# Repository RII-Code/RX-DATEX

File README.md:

# RX-DATEX (DATA EXCHANGE)

Perangkat IoT industrial yang berfungsi sebagai sistem gateway dan data exchange untuk komunikasi, monitoring, dan pertukaran data antar perangkat industri.

## Fitur

- Gateway Modbus RTU ↔ TCP/IP
- Pengirim data telemetry melalui jaringan 4G LTE
- Sistem monitoring device industri
- Data logger dan remote monitoring
- MQTT / HTTP data exchange
- Remote access dan konfigurasi perangkat

---

## Author

Ruang Industri Indonesia  
Industrial Automation & Robotics

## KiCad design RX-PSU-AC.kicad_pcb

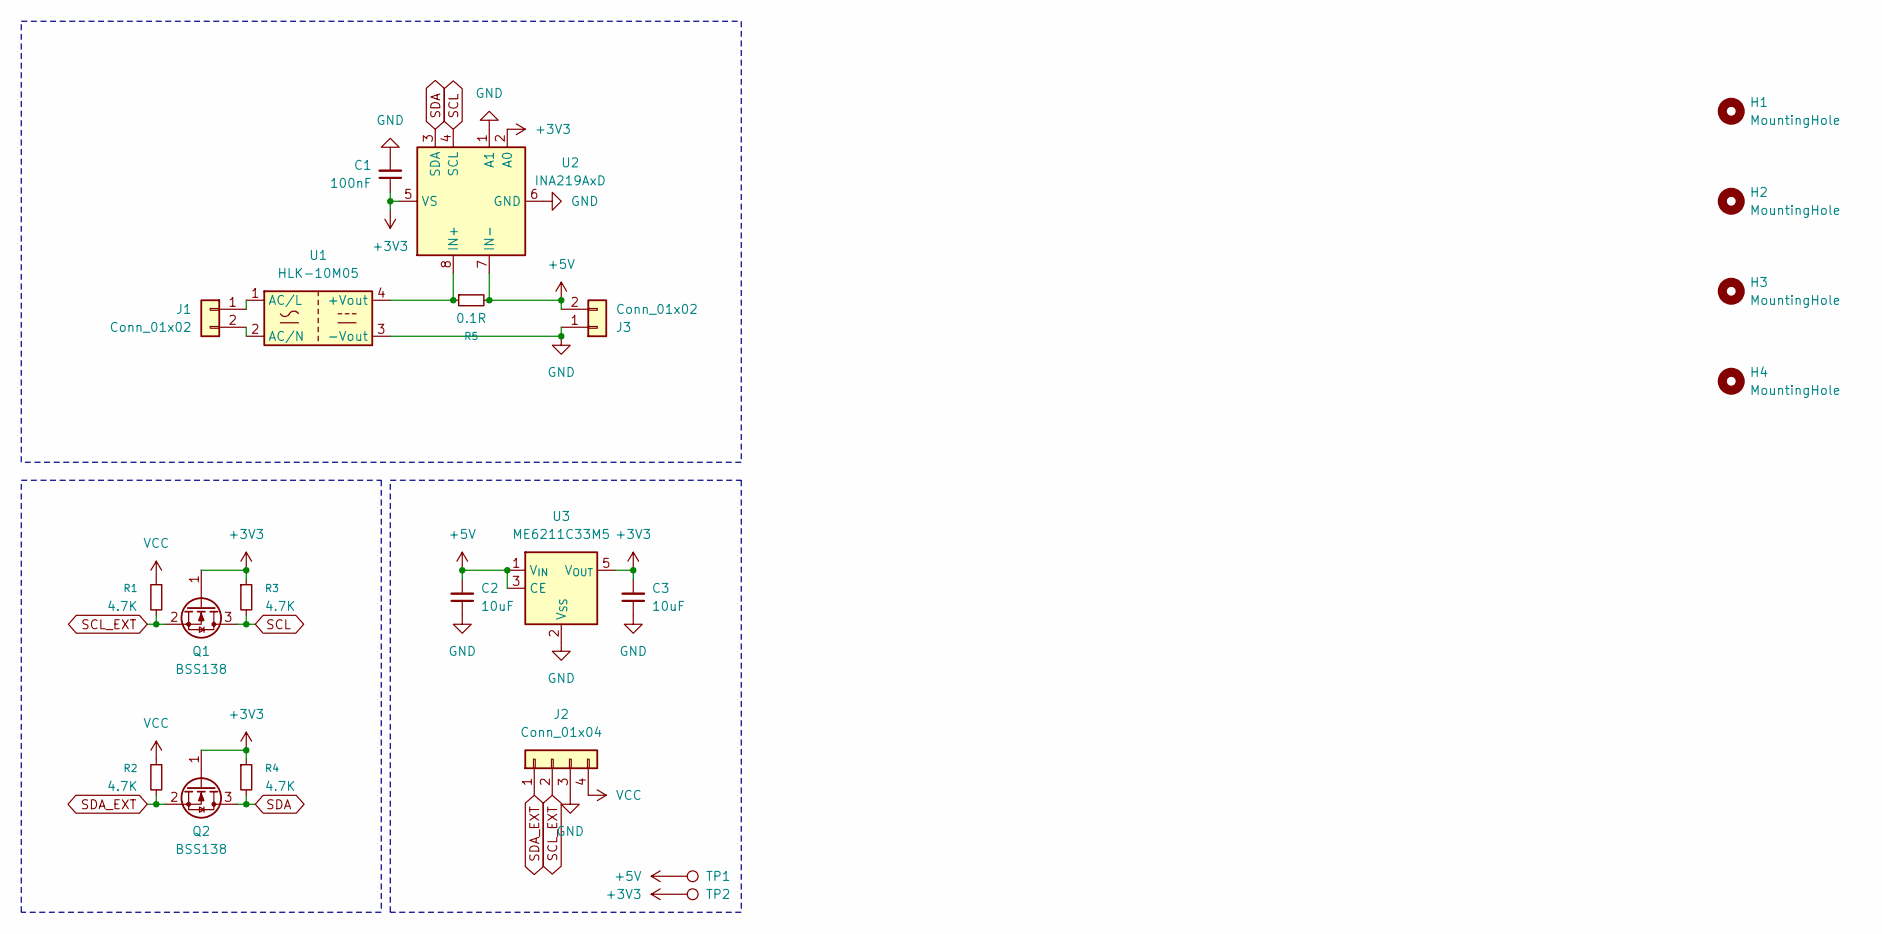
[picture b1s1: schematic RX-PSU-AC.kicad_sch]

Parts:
C1: 100nF; C_0805_2012Metric
C2, C3: 10uF; C_1206_3216Metric
H1, H2, H3, H4: MountingHole; MountingHole_3mm
J1: Conn_01x02; PhoenixContact_MC_1,5_2-G-5.08_1x02_P5.08mm_Horizontal
J2: Conn_01x04; JST_XH_B4B-XH-A_1x04_P2.50mm_Vertical
J3: Conn_01x02; JST_XH_B2B-XH-A_1x02_P2.50mm_Vertical
Q1, Q2: BSS138; SOT-23
R1, R2, R3, R4: 4.7K; R_0805_2012Metric
R5: 0.1R; R_2512_6332Metric
TP1, TP2: TestPoint; TestPoint_Pad_D1.0mm
U1: HLK-10M05; Converter_ACDC_Hi-Link_HLK-10Mxx
U2: INA219AxD; SOIC-8_3.9x4.9mm_P1.27mm
U3: ME6211C33M5; SOT-23-5

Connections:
+3V3: C1.1, C3.2, Q1.1 (G), Q2.1 (G), R3.1, R4.1, TP2.1 (1_1), U2.2 (A0), U2.5 (VS), U3.5 (V_{OUT})
+5V: C2.2, J3.2, R5.2, TP1.1 (1_1), U2.7 (IN-), U3.1 (V_{IN}), U3.3 (CE)
GND: C1.2, C2.1, C3.1, J2.3, J3.1, U1.3 (-Vout), U2.1 (A1), U2.6 (GND), U3.2 (V_{SS})
unnamed: J1.1, U1.1 (AC/L)
unnamed: J1.2, U1.2 (AC/N)
unnamed: R5.1, U1.4 (+Vout), U2.8 (IN+)
SCL: Q1.3 (D), R3.2, U2.4 (SCL)
SCL_EXT: J2.2, Q1.2 (S), R1.2
SDA: Q2.3 (D), R4.2, U2.3 (SDA)
SDA_EXT: J2.1, Q2.2 (S), R2.2
VCC: J2.4, R1.1, R2.1

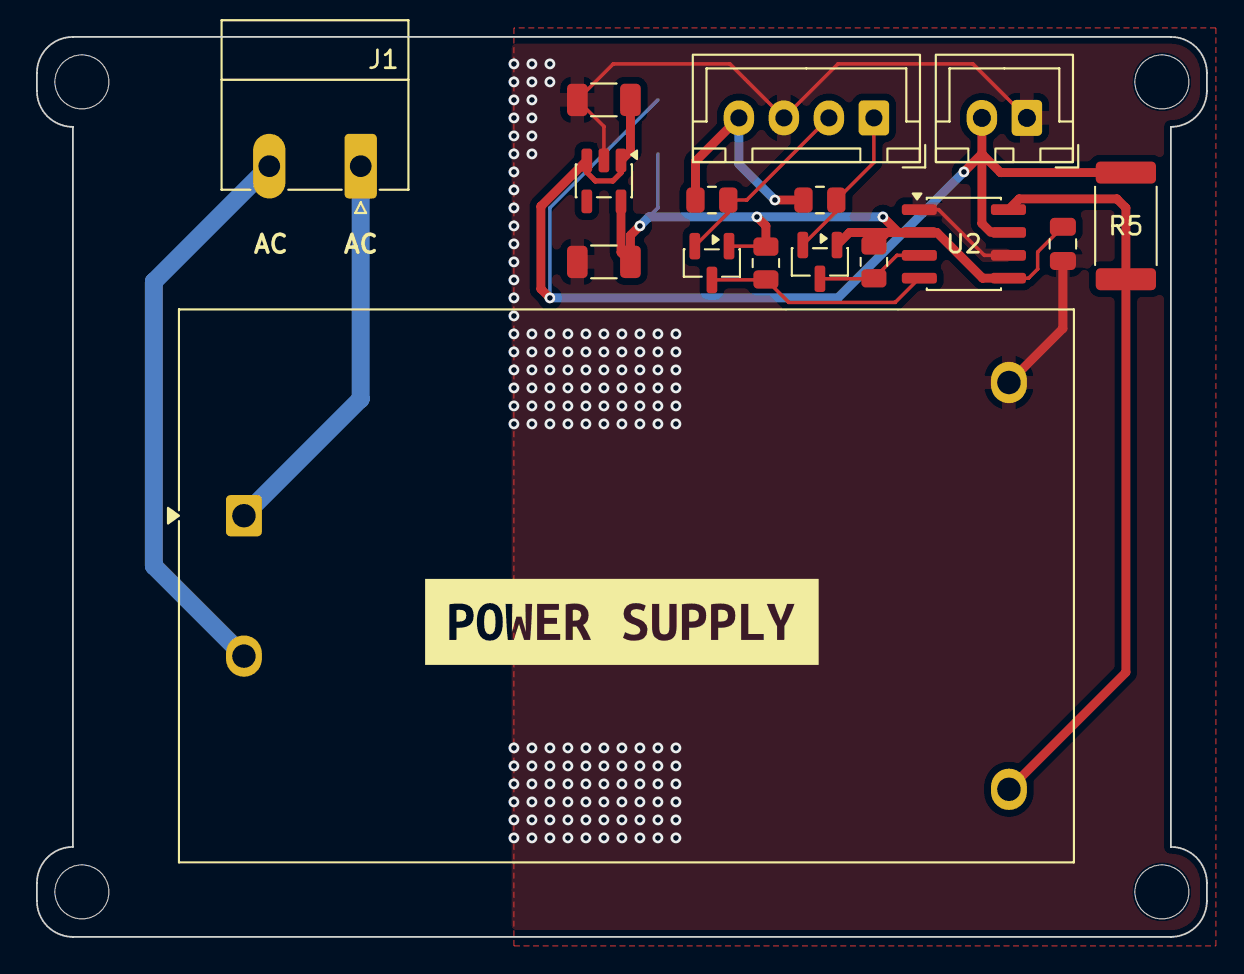
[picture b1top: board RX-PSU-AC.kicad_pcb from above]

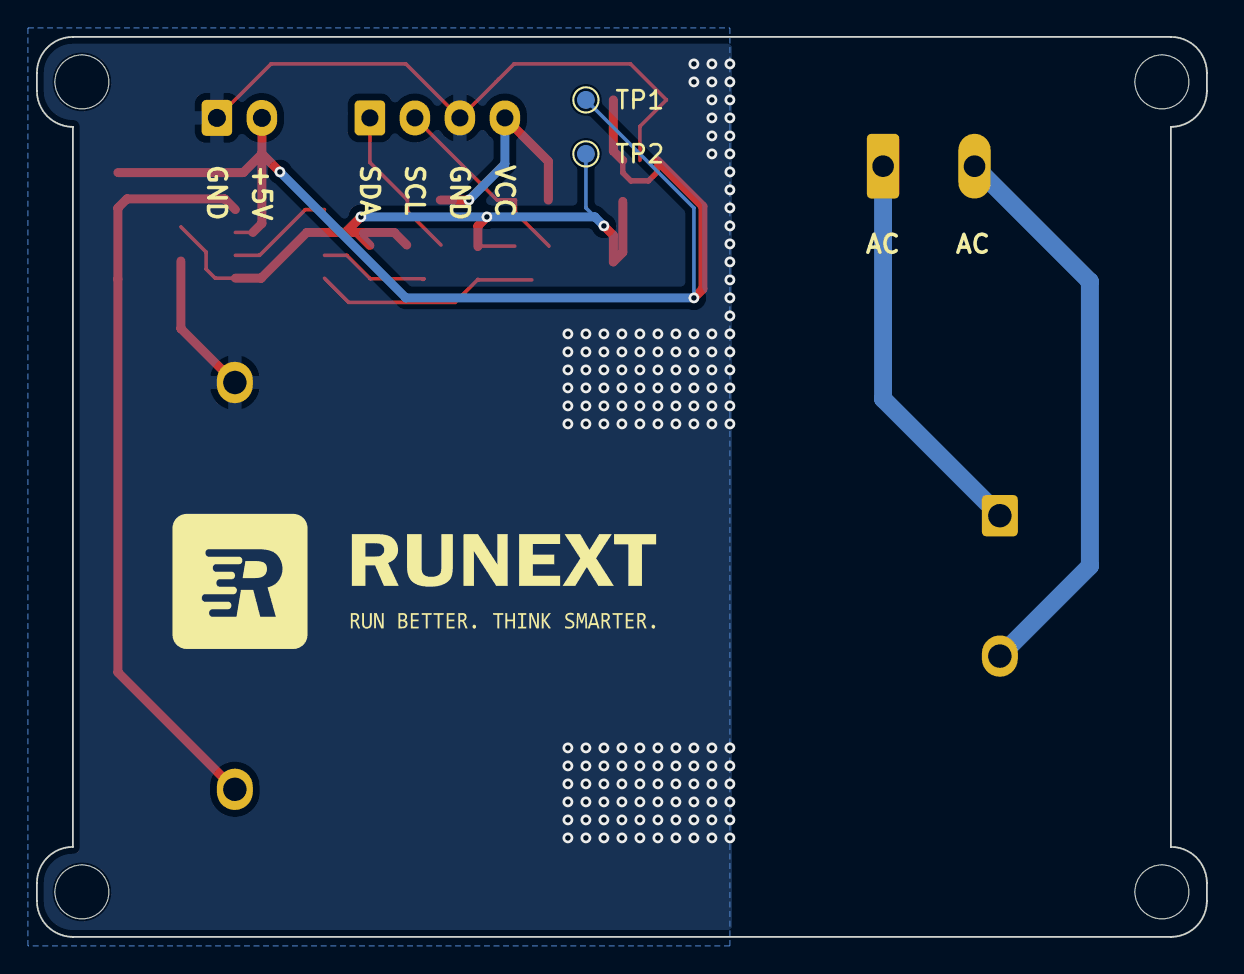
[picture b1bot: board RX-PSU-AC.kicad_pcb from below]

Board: 2 copper layers, 65.0 x 50.0 mm, 23 parts (2 on the bottom side), 11 nets.

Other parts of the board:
kibuzzard-6A0C9131: G***; kibuzzard-6A0C9131

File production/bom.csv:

Designator,Footprint,Quantity,Value,LCSC Part #
C1,0805,1,100nF,
"C2, C3",1206,2,10uF,
J1,"PhoenixContact_MC_1,5_2-G-5.08_1x02_P5.08mm_Horizontal",1,Conn_01x02,
J2,JST_XH_B4B-XH-A_1x04_P2.50mm_Vertical,1,Conn_01x04,
J3,JST_XH_B2B-XH-A_1x02_P2.50mm_Vertical,1,Conn_01x02,
"Q1, Q2",SOT-23,2,BSS138,
"R1, R2, R3, R4",0805,4,4.7K,
R5,2512,1,0.1R,
"TP1, TP2",TestPoint_Pad_D1.0mm,2,TestPoint,
U1,Converter_ACDC_Hi-Link_HLK-10Mxx,1,HLK-10M05,
U2,SOIC-8_3.9x4.9mm_P1.27mm,1,INA219AxD,
U3,SOT-23-5,1,ME6211C33M5,

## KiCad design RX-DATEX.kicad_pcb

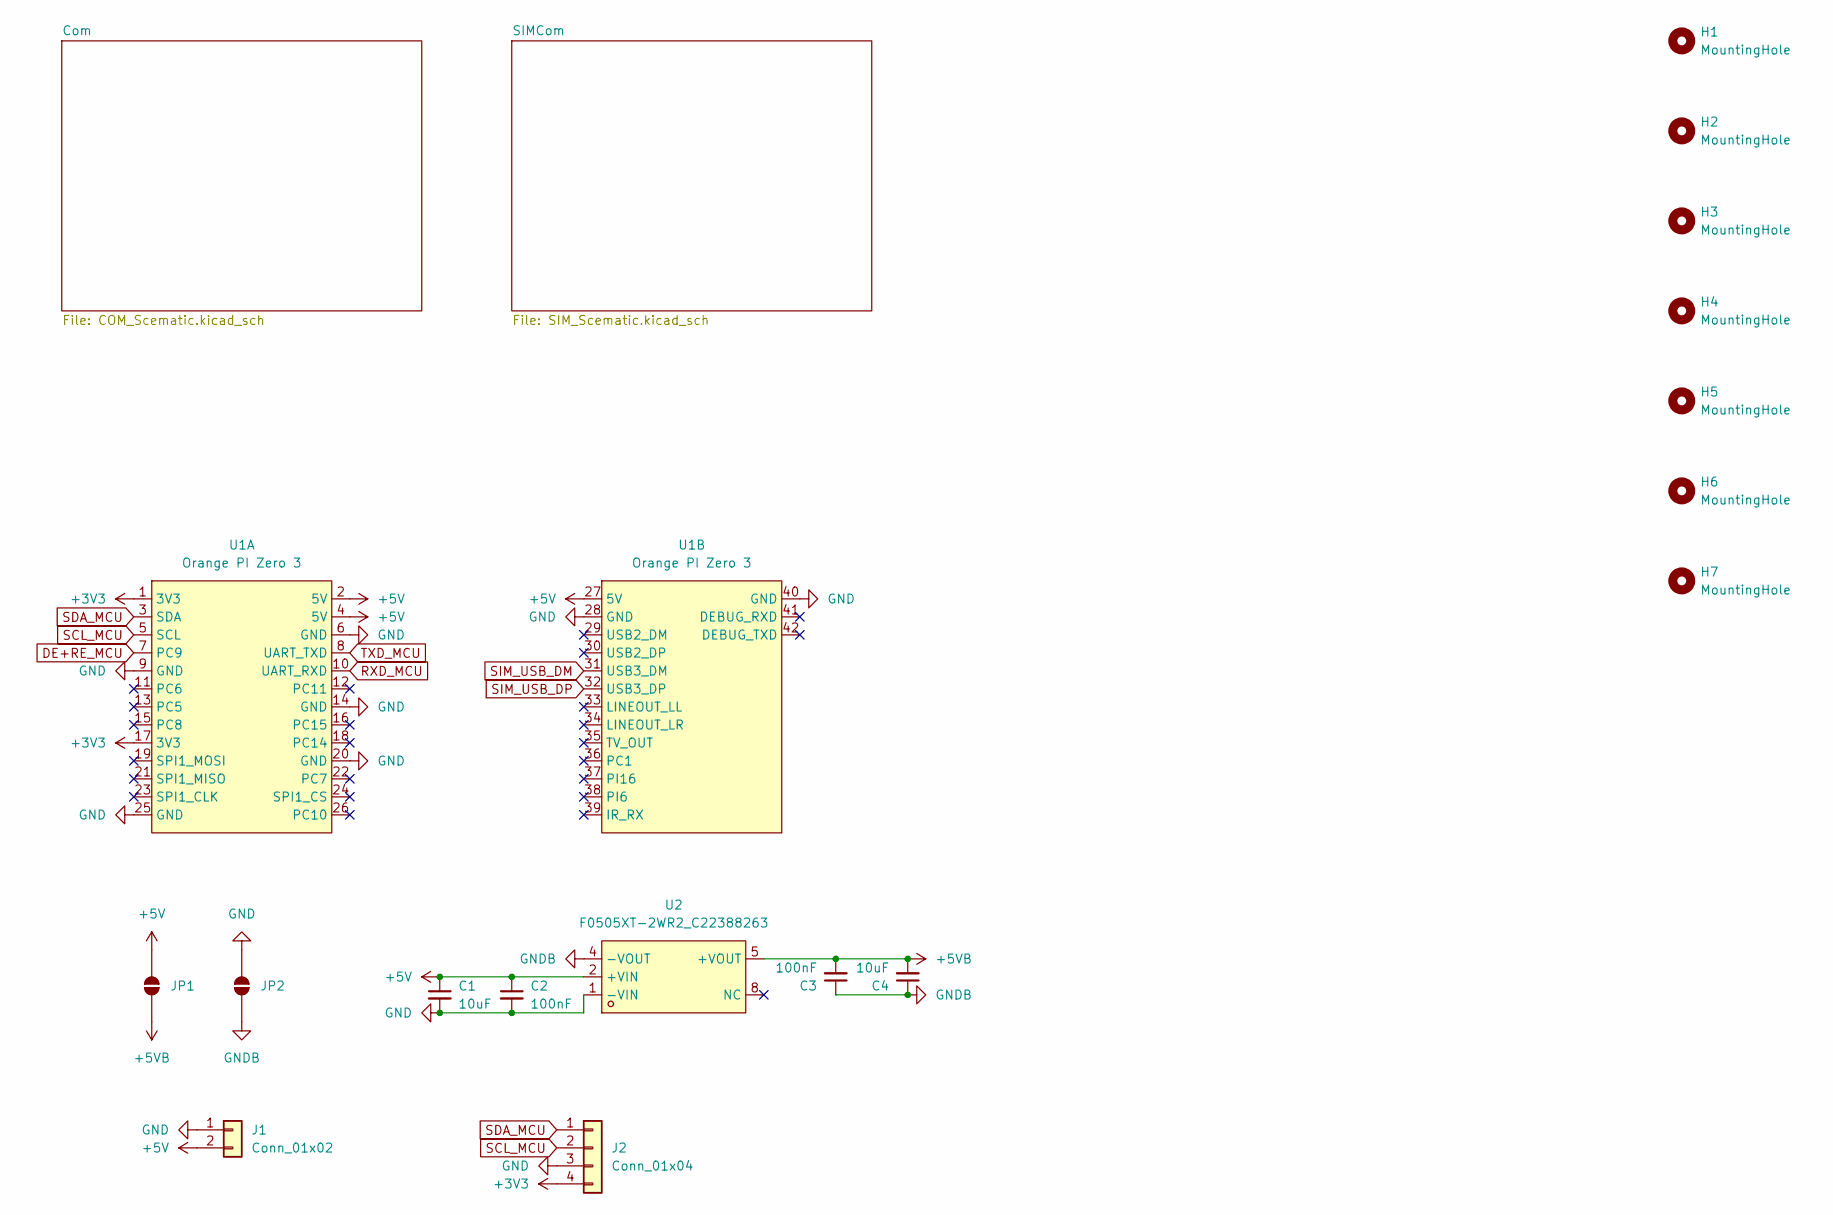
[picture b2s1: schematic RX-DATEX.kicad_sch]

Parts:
C1, C4: 10uF; C_0603_1608Metric
C2, C3: 100nF; C_0603_1608Metric
H1, H2, H3, H4, H5, H6, H7: MountingHole; MountingHole_3mm
J1: Conn_01x02; JST_XH_B2B-XH-A_1x02_P2.50mm_Vertical
J2: Conn_01x04; JST_XH_B4B-XH-A_1x04_P2.50mm_Vertical
JP1, JP2: SolderJumper_2_Open; SolderJumper-2_P1.3mm_Open_RoundedPad1.0x1.5mm
U1: Orange PI Zero 3; OPIZ3
U2: F0505XT-2WR2_C22388263; PWRM-SMD_FXXXXXT-2WR2; MPN F0505XT-2WR2; LCSC Part C22388263

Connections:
+3V3: J2.4, U1.1 (3V3), U1.17 (3V3); also elsewhere on the board
+5V: C1.1, C2.1, J1.2, JP1.2 (B), U1.2 (5V), U1.4 (5V), U1.27 (5V), U2.2 (+VIN); also elsewhere on the board
+5VB: C3.2, C4.2, JP1.1 (A), U2.5 (+VOUT); also elsewhere on the board
DE+RE_MCU: U1.7 (PC9); also elsewhere on the board
GND: C1.2, C2.2, J1.1, J2.3, JP2.2 (B), U1.6 (GND), U1.9 (GND), U1.14 (GND), U1.20 (GND), U1.25 (GND), U1.28 (GND), U1.40 (GND), U2.1 (-VIN); also elsewhere on the board
GNDB: C3.1, C4.1, JP2.1 (A), U2.4 (-VOUT); also elsewhere on the board
RXD_MCU: U1.10 (UART_RXD); also elsewhere on the board
SCL_MCU: J2.2, U1.5 (SCL); also elsewhere on the board
SDA_MCU: J2.1, U1.3 (SDA); also elsewhere on the board
SIM_USB_DM: U1.31 (USB3_DM); also elsewhere on the board
SIM_USB_DP: U1.32 (USB3_DP); also elsewhere on the board
TXD_MCU: U1.8 (UART_TXD); also elsewhere on the board

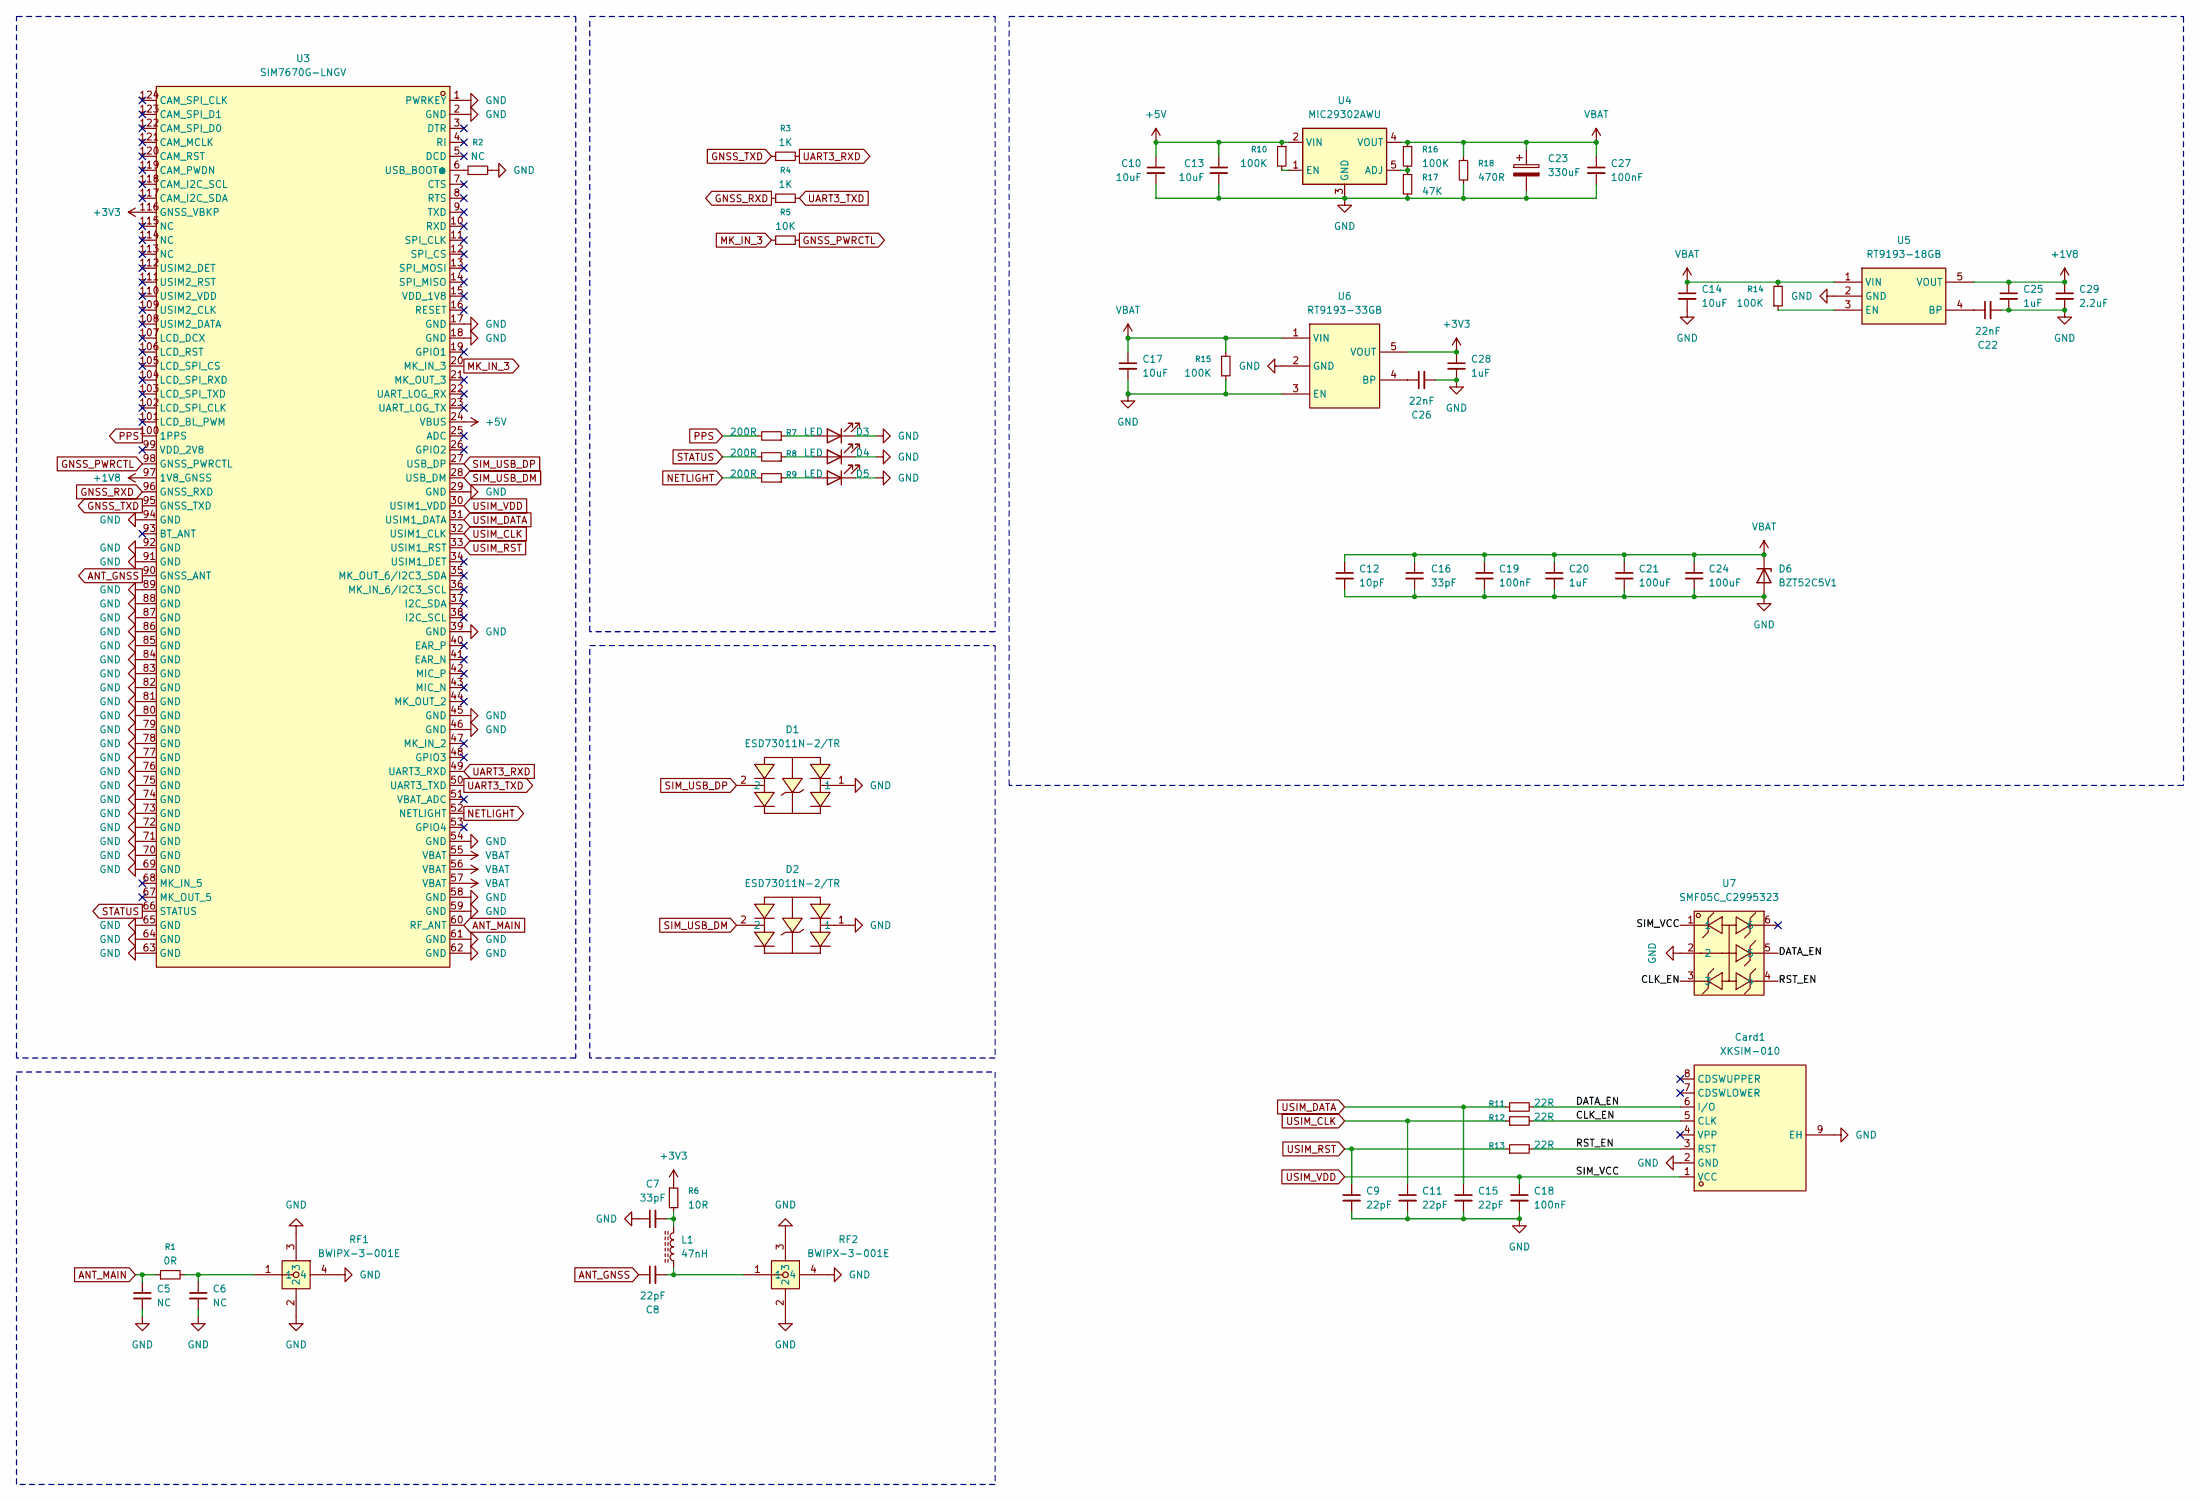
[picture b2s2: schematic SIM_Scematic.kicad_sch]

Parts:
C5, C6: NC; C_0603_1608Metric
C7, C16: 33pF; C_0603_1608Metric
C8, C9, C11, C15: 22pF; C_0603_1608Metric
C10, C13, C14, C17: 10uF; C_0603_1608Metric
C12: 10pF; C_0603_1608Metric
C18, C19, C27: 100nF; C_0603_1608Metric
C20, C25, C28: 1uF; C_0603_1608Metric
C21, C24: 100uF; C_0805_2012Metric
C22, C26: 22nF; C_0603_1608Metric
C23: 330uF; CP_EIA-7343-31_Kemet-D
C29: 2.2uF; C_0603_1608Metric
Card1: XKSIM-010; SIM-SMD_XKSIM-010; MPN XKSIM-010; LCSC Part C437039
D1, D2: ESD73011N-2/TR; DFN1006-2L-BI; MPN ESD73011N-2/TR; LCSC Part C506104
D3, D4, D5: LED; LED_1206_3216Metric
D6: BZT52C5V1; D_SOD-123
L1: 47nH; L_0603_1608Metric
R1: 0R; R_0603_1608Metric
R2: NC; R_0603_1608Metric
R3, R4: 1K; R_0603_1608Metric
R5: 10K; R_0603_1608Metric
R6: 10R; R_0603_1608Metric
R7, R8, R9: 200R; R_0603_1608Metric
R10, R14, R15, R16: 100K; R_0603_1608Metric
R11, R12, R13: 22R; R_0603_1608Metric
R17: 47K; R_0603_1608Metric
R18: 470R; R_0603_1608Metric
RF1, RF2: BWIPX-3-001E; IPEX-SMD_BWIPX-3-001E-1; MPN BWIPX-3-001E; LCSC Part C784400
U3: SIM7670G-LNGV; LCC-124_L24.0-W24.0-P1.0-TL; MPN SIM7670G-LNGV; LCSC Part C45935408
U4: MIC29302AWU; TO-263-5_TabPin3
U5: RT9193-18GB; SOT-23-5_L3.0-W1.7-P0.95-LS2.8-BR; MPN RT9193-18GB; LCSC Part C27416
U6: RT9193-33GB; SOT-23-5_L3.0-W1.7-P0.95-LS2.8-BL; MPN RT9193-33GB; LCSC Part C15651
U7: SMF05C_C2995323; SOT-363_L2.1-W1.3-P0.65-LS2.1-BL; MPN SMF05C; LCSC Part C2995323

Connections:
+1V8: C25.1, C29.1, U3.97 (1V8_GNSS), U5.5 (VOUT)
+3V3: C28.1, R6.1, U3.116 (GNSS_VBKP), U6.5 (VOUT); also elsewhere on the board
+5V: C10.1, C13.1, R10.1, U3.24 (VBUS), U4.2 (VIN); also elsewhere on the board
/SIMCom/CLK_EN: Card1.5 (CLK), R12.2, U7.3
/SIMCom/DATA_EN: Card1.6 (I/O), R11.2, U7.5
/SIMCom/RST_EN: Card1.3 (RST), R13.2, U7.4
ANT_GNSS: C8.1, U3.90 (GNSS_ANT)
ANT_MAIN: C5.1, R1.1, U3.60 (RF_ANT)
GND: C5.2, C6.2, C7.1, C9.2, C10.2, C11.2, C12.2, C13.2, C14.2, C15.2, C16.2, C17.2, C18.2, C19.2, C20.2, C21.2, C22.2, C23.2, C24.2, C25.2, C26.2, C27.2, C28.2, C29.2, Card1.2 (GND), Card1.9 (EH), D1.1, D2.1, D3.1 (K), D4.1 (K), D5.1 (K), D6.2 (A), R2.2, R15.1, R17.2, R18.2, RF1.2, RF1.3, RF1.4, RF2.2, RF2.3, RF2.4, U3.1 (PWRKEY), U3.2 (GND), U3.17 (GND), U3.18 (GND), U3.29 (GND), U3.39 (GND), U3.45 (GND), U3.46 (GND), U3.54 (GND), U3.58 (GND), U3.59 (GND), U3.61 (GND), U3.62 (GND), U3.63 (GND), U3.64 (GND), U3.65 (GND), U3.69 (GND), U3.70 (GND), U3.71 (GND), U3.72 (GND), U3.73 (GND), U3.74 (GND), U3.75 (GND), U3.76 (GND), U3.77 (GND), U3.78 (GND), U3.79 (GND), U3.80 (GND), U3.81 (GND), U3.82 (GND), U3.83 (GND), U3.84 (GND), U3.85 (GND), U3.86 (GND), U3.87 (GND), U3.88 (GND), U3.89 (GND), U3.91 (GND), U3.92 (GND), U3.94 (GND), U4.3 (GND), U5.2 (GND), U6.2 (GND), U6.3 (EN), U7.2; also elsewhere on the board
GNSS_PWRCTL: R5.2, U3.98 (GNSS_PWRCTL)
GNSS_RXD: R4.1, U3.96 (GNSS_RXD)
GNSS_TXD: R3.1, U3.95 (GNSS_TXD)
MK_IN_3: R5.1, U3.20 (MK_IN_3)
NETLIGHT: R9.2, U3.52 (NETLIGHT)
unnamed: C6.1, R1.2, RF1.1
unnamed: C7.2, L1.2, R6.2
unnamed: C8.2, L1.1, RF2.1
unnamed: D3.2 (A), R7.1
unnamed: D4.2 (A), R8.1
unnamed: D5.2 (A), R9.1
unnamed: R2.1, U3.6 (USB_BOOT●)
unnamed: R16.2, R17.1, U4.5 (ADJ)
unnamed: R10.2, U4.1 (EN)
unnamed: C22.1, U5.4 (BP)
unnamed: R14.1, U5.3 (EN)
unnamed: C26.1, U6.4 (BP)
PPS: R7.2, U3.100 (1PPS)
SIM_USB_DM: D2.2, U3.28 (USB_DM); also elsewhere on the board
SIM_USB_DP: D1.2, U3.27 (USB_DP); also elsewhere on the board
STATUS: R8.2, U3.66 (STATUS)
UART3_RXD: R3.2, U3.49 (UART3_RXD)
UART3_TXD: R4.2, U3.50 (UART3_TXD)
USIM_CLK: C11.1, R12.1, U3.32 (USIM1_CLK)
USIM_DATA: C15.1, R11.1, U3.31 (USIM1_DATA)
USIM_RST: C9.1, R13.1, U3.33 (USIM1_RST)
USIM_VDD: C18.1, Card1.1 (VCC), U3.30 (USIM1_VDD), U7.1
VBAT: C12.1, C14.1, C16.1, C17.1, C19.1, C20.1, C21.1, C23.1, C24.1, C27.1, D6.1 (K), R14.2, R15.2, R16.1, R18.1, U3.55 (VBAT), U3.56 (VBAT), U3.57 (VBAT), U4.4 (VOUT), U5.1 (VIN), U6.1 (VIN)

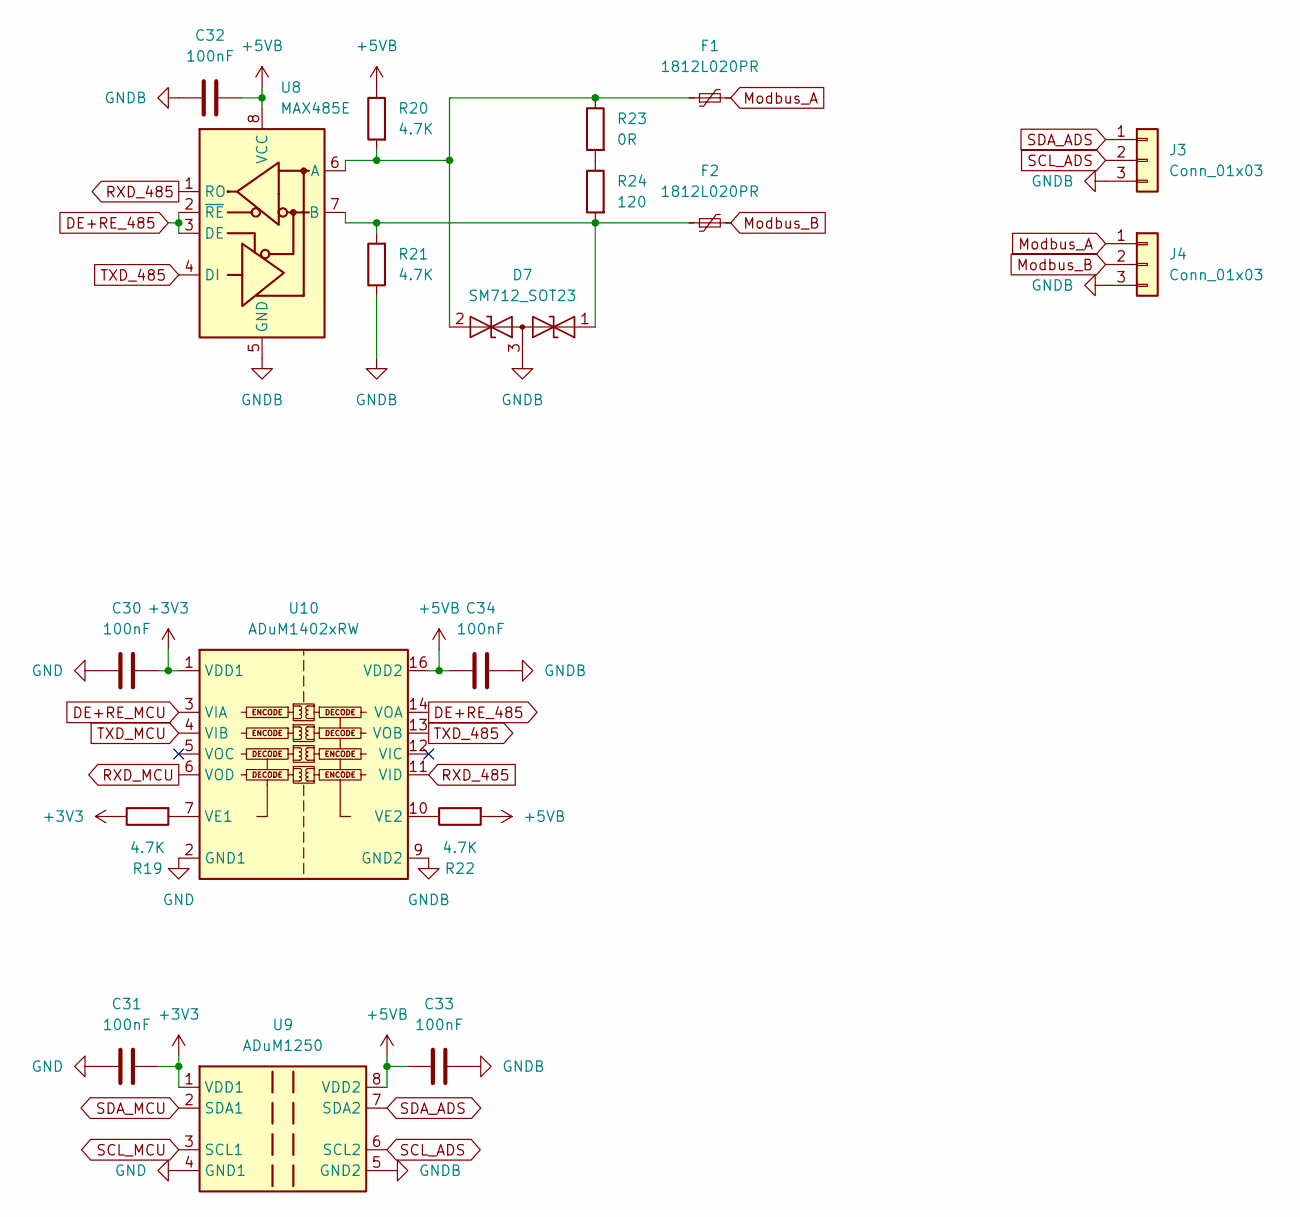
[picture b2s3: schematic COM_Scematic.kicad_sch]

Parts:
C30, C31, C32, C33, C34: 100nF; C_0603_1608Metric_Pad1.08x0.95mm_HandSolder
D7: SM712_SOT23; SOT-23
F1, F2: 1812L020PR; Fuse_1812_4532Metric
J3, J4: Conn_01x03; PhoenixContact_MC_1,5_3-G-3.81_1x03_P3.81mm_Horizontal
R19, R20, R21, R22: 4.7K; R_0603_1608Metric_Pad0.98x0.95mm_HandSolder
R23: 0R; R_0603_1608Metric_Pad0.98x0.95mm_HandSolder
R24: 120; R_0603_1608Metric_Pad0.98x0.95mm_HandSolder
U8: MAX485E; SOIC-8_3.9x4.9mm_P1.27mm
U9: ADuM1250; SOIC-8_3.9x4.9mm_P1.27mm
U10: ADuM1402xRW; SOIC-16W_7.5x10.3mm_P1.27mm

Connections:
+3V3: C30.2, C31.2, R19.1, U9.1 (VDD1), U10.1 (VDD1); also elsewhere on the board
+5VB: C32.2, C33.2, C34.2, R20.1, R22.2, U8.8 (VCC), U9.8 (VDD2), U10.16 (VDD2); also elsewhere on the board
DE+RE_485: U8.2 (~RE), U8.3 (DE), U10.14 (VOA)
DE+RE_MCU: U10.3 (VIA); also elsewhere on the board
GND: C30.1, C31.1, U9.4 (GND1), U10.2 (GND1), U10.8 (GND1); also elsewhere on the board
GNDB: C32.1, C33.1, C34.1, D7.3 (common), J3.3, J4.3, R21.1, U8.5 (GND), U9.5 (GND2), U10.9 (GND2), U10.15 (GND2); also elsewhere on the board
Modbus_A: F1.2, J4.1
Modbus_B: F2.2, J4.2
unnamed: D7.1 (A1), F2.1, R21.2, R24.2, U8.7 (B)
unnamed: D7.2 (A2), F1.1, R20.2, R23.1, U8.6 (A)
unnamed: R23.2, R24.1
unnamed: R19.2, U10.7 (VE1)
unnamed: R22.1, U10.10 (VE2)
RXD_485: U8.1 (RO), U10.11 (VID)
RXD_MCU: U10.6 (VOD); also elsewhere on the board
SCL_ADS: J3.2, U9.6 (SCL2)
SCL_MCU: U9.3 (SCL1); also elsewhere on the board
SDA_ADS: J3.1, U9.7 (SDA2)
SDA_MCU: U9.2 (SDA1); also elsewhere on the board
TXD_485: U8.4 (DI), U10.13 (VOB)
TXD_MCU: U10.4 (VIB); also elsewhere on the board

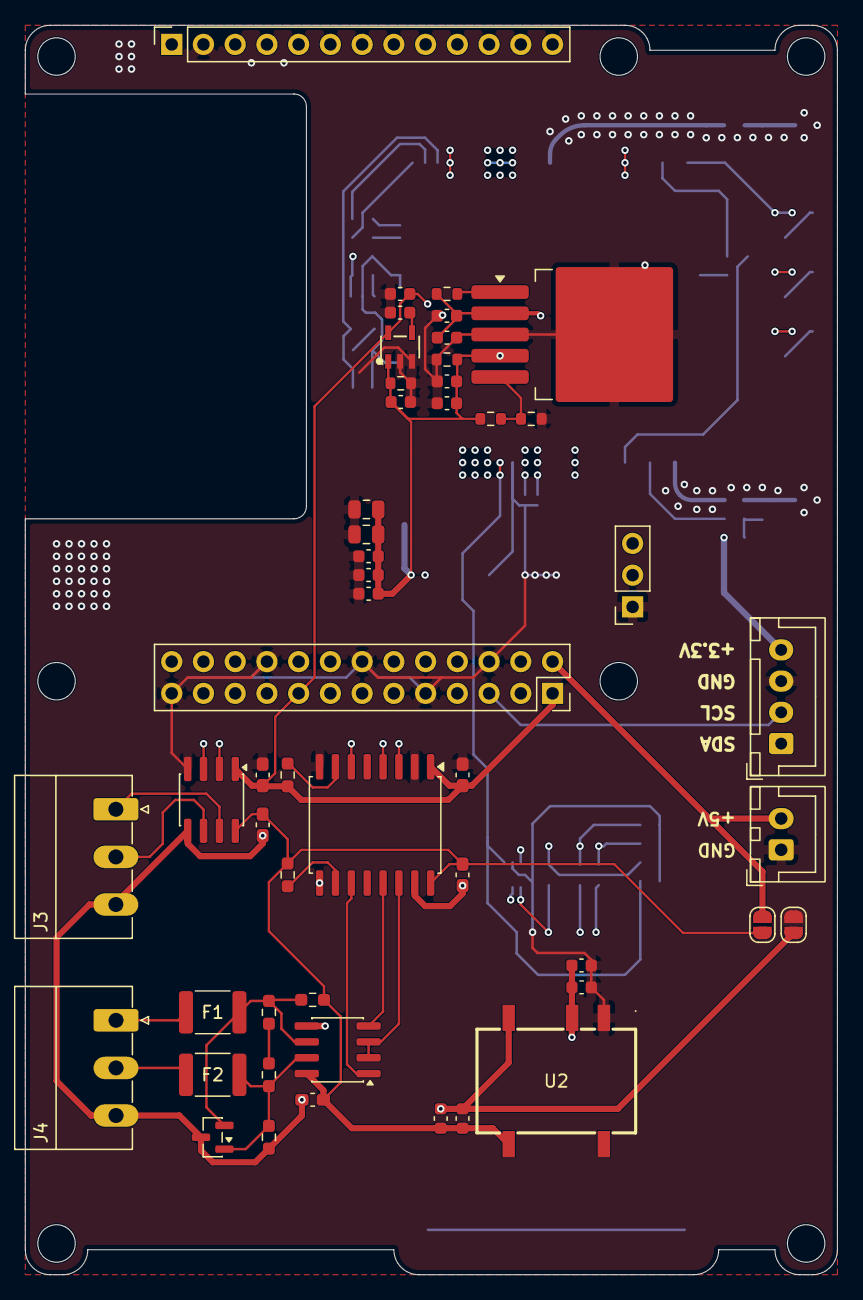
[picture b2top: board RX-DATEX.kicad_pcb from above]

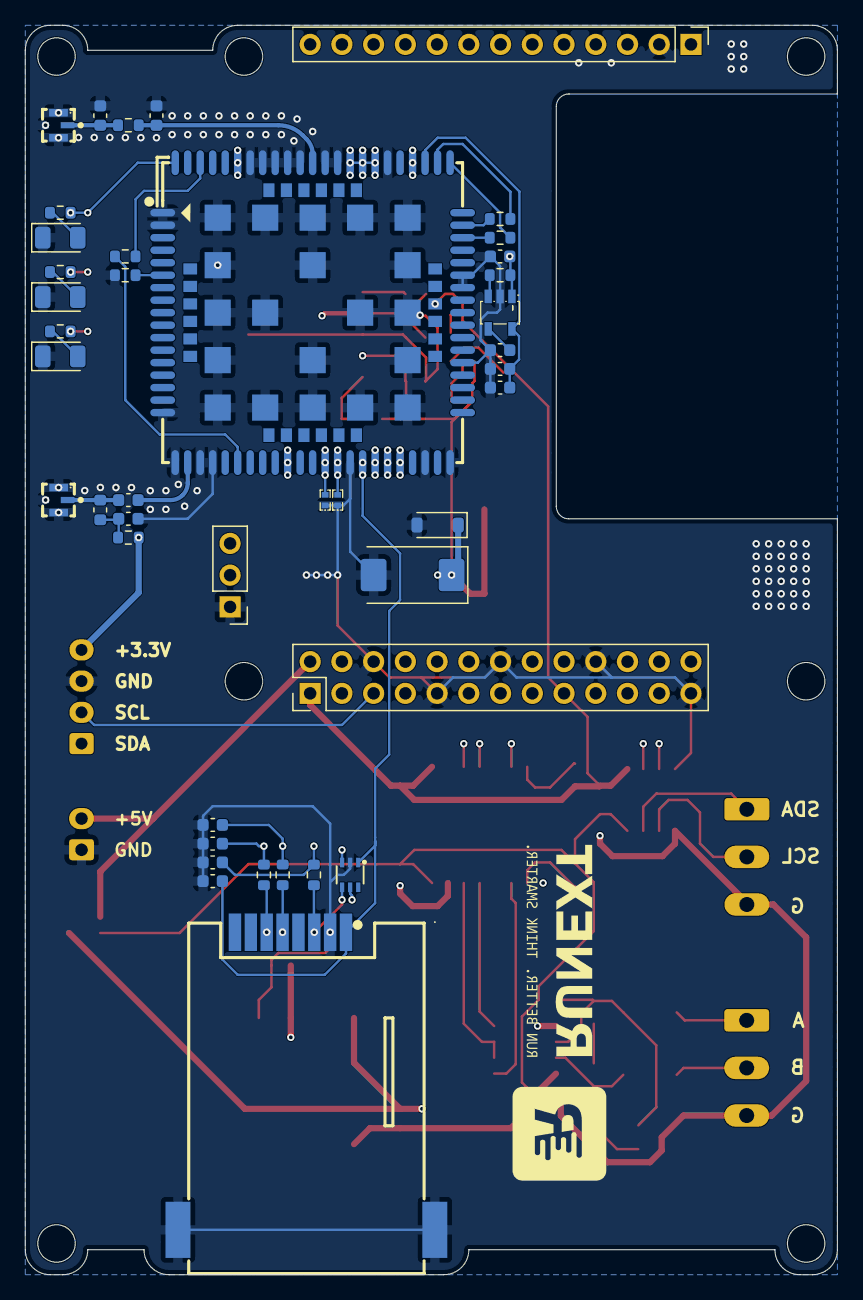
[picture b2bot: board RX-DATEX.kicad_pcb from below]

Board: 4 copper layers, 65.0 x 100.0 mm, 94 parts (40 on the bottom side), 56 nets.

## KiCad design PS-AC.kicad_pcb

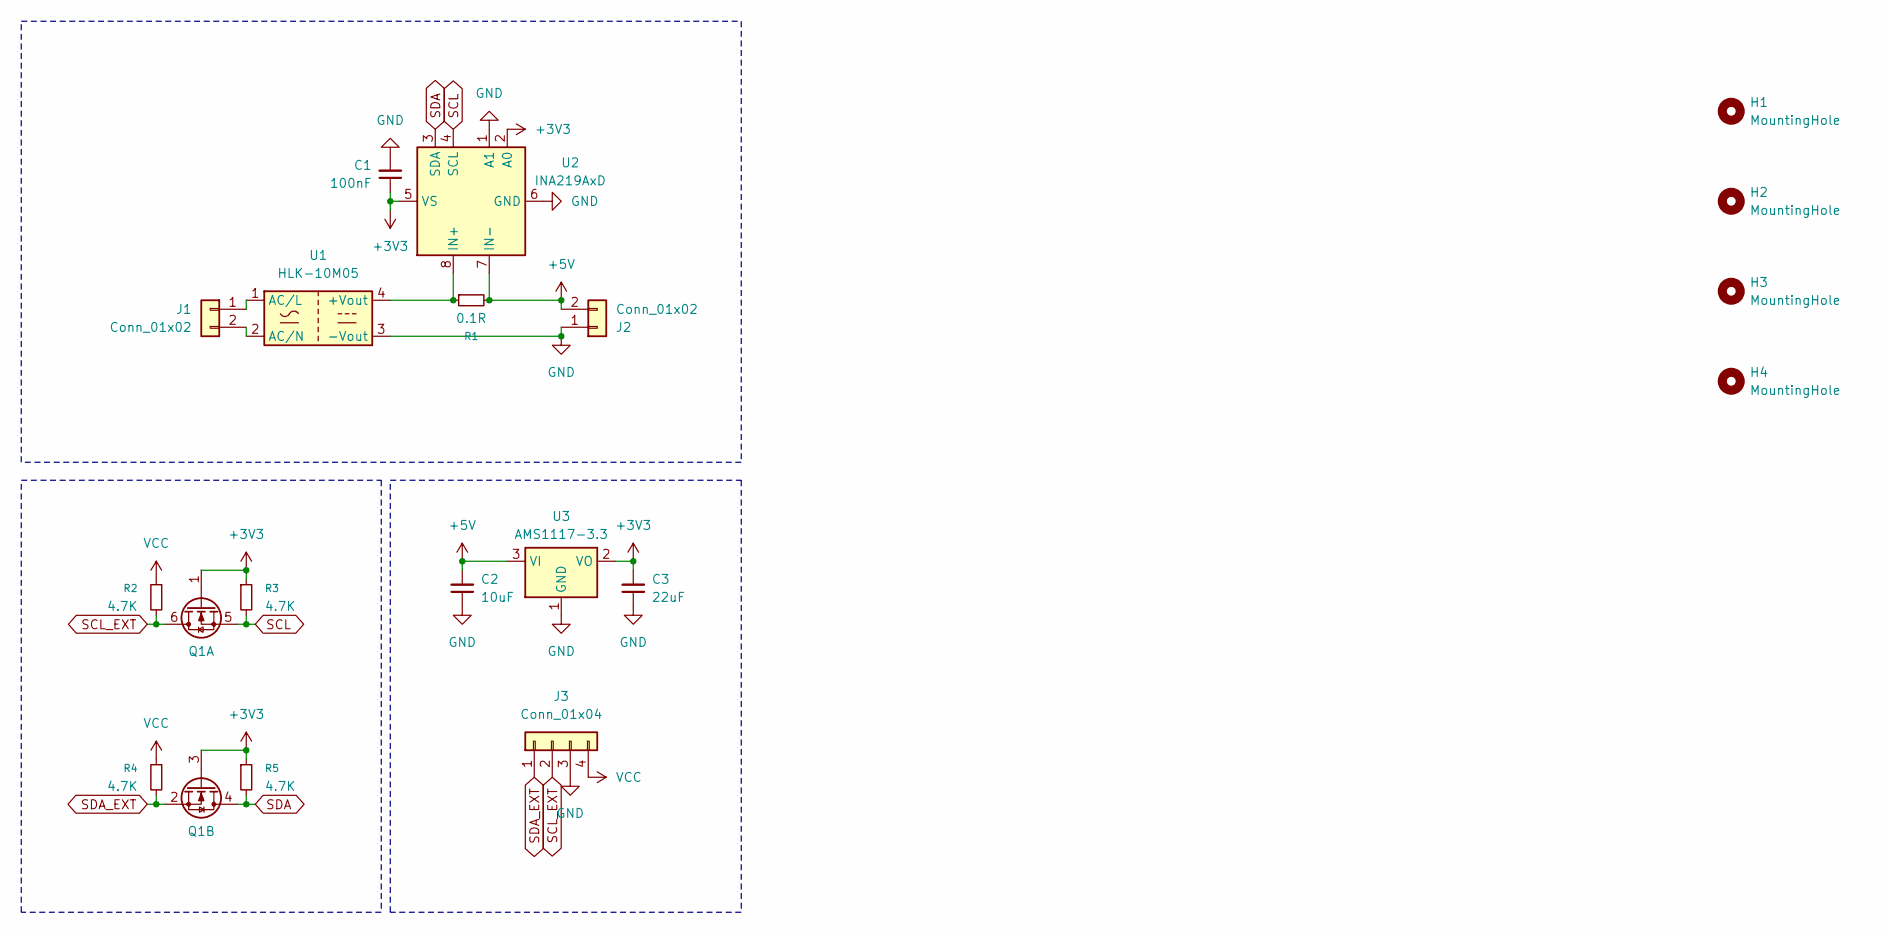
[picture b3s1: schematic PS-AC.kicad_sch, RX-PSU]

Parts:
C1: 100nF; C_0603_1608Metric
C2: 10uF; C_0603_1608Metric
C3: 22uF; C_0603_1608Metric
H1, H2, H3, H4: MountingHole; MountingHole_3mm
J1: Conn_01x02; PhoenixContact_MC_1,5_2-G-5.08_1x02_P5.08mm_Horizontal
J2: Conn_01x02; JST_XH_B2B-XH-A_1x02_P2.50mm_Vertical
J3: Conn_01x04; JST_XH_B4B-XH-A_1x04_P2.50mm_Vertical
Q1: NTZD3154NT1G; SOT-563
R1: 0.1R; R_1206_3216Metric
R2, R3, R4, R5: 4.7K; R_0603_1608Metric
U1: HLK-10M05; Converter_ACDC_Hi-Link_HLK-10Mxx
U2: INA219AxD; SOIC-8_3.9x4.9mm_P1.27mm
U3: AMS1117-3.3; SOT-223-3_TabPin2

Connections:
+3V3: C1.1, C3.2, Q1.1 (G), Q1.3 (G), R3.1, R5.1, U2.2 (A0), U2.5 (VS), U3.2 (VO)
+5V: C2.2, J2.2, R1.2, U2.7 (IN-), U3.3 (VI)
GND: C1.2, C2.1, C3.1, J2.1, J3.3, U1.3 (-Vout), U2.1 (A1), U2.6 (GND), U3.1 (GND)
unnamed: J1.1, U1.1 (AC/L)
unnamed: J1.2, U1.2 (AC/N)
unnamed: R1.1, U1.4 (+Vout), U2.8 (IN+)
SCL: Q1.5 (S), R3.2, U2.4 (SCL)
SCL_EXT: J3.2, Q1.6 (D), R2.2
SDA: Q1.4 (D), R5.2, U2.3 (SDA)
SDA_EXT: J3.1, Q1.2 (S), R4.2
VCC: J3.4, R2.1, R4.1

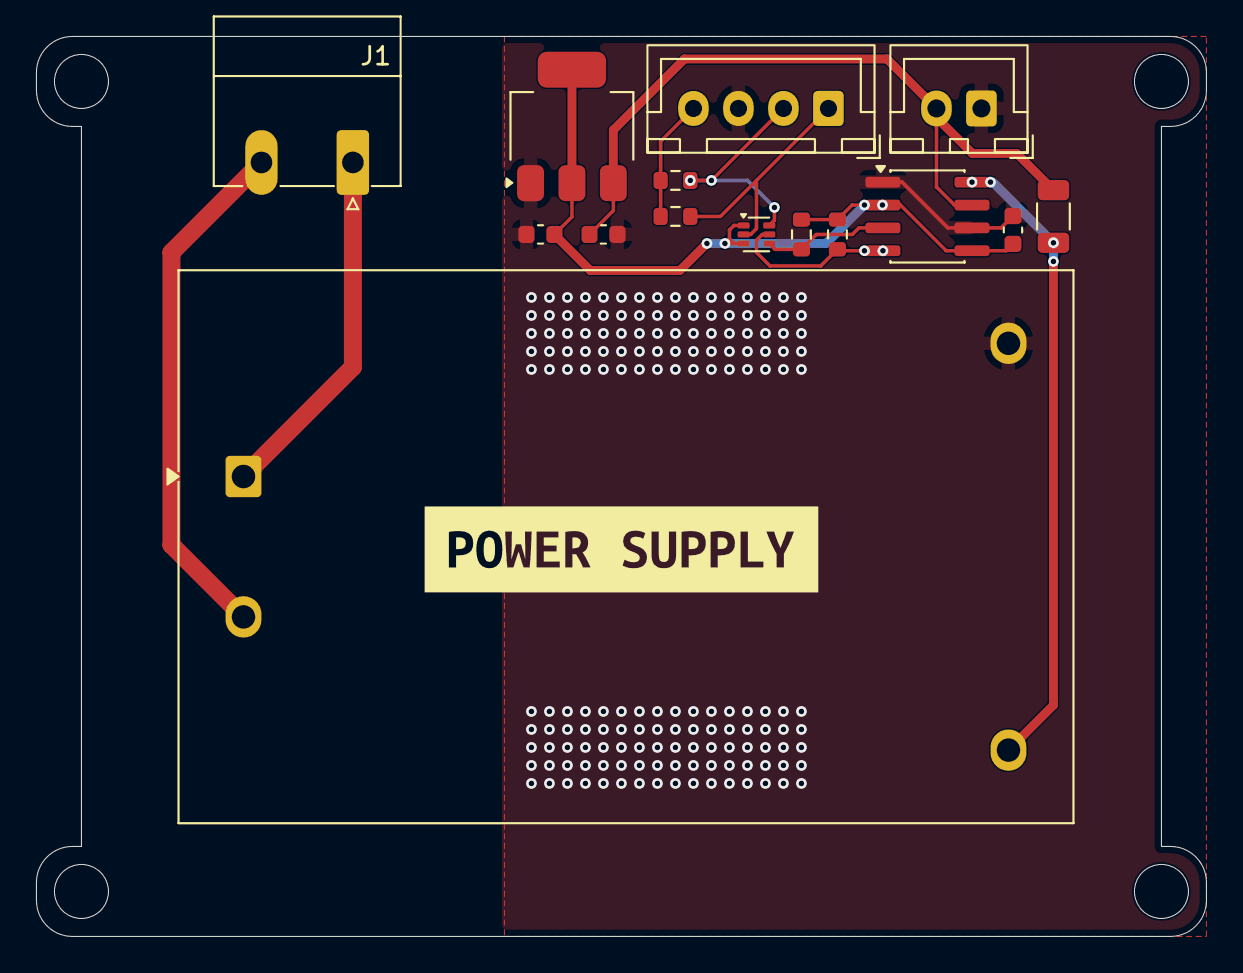
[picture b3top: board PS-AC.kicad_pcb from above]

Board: 2 copper layers, 65.0 x 50.0 mm, 20 parts (0 on the bottom side), 11 nets.

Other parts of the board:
kibuzzard-6A04000D: G***; kibuzzard-6A04000D

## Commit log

2026-05-12 Update Skematic & PCB Desian
2026-05-12 Update Skematic
2026-05-19 clear
